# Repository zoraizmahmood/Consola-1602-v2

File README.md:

# Consola 1602 · v2

> La segunda versión de la [Consola 1602](https://github.com/zoraizmahmood/Consola-1602): el mismo firmware, pero ahora sobre una **PCB propia** diseñada en KiCad y fabricada por **PCBWay**. Adiós a la protoboard y a los cables sueltos.

<p align="center"><sub>El LCD y los botones colocados en su sitio, todavía sin soldar (ver <a href="#estado-del-montaje">estado del montaje</a>).</sub></p>

La v1 era un Arduino Uno, un LCD de 16x2, cinco botones y un zumbador unidos con cables dupont. Funcionaba, pero cualquier golpe soltaba un cable y no había forma de meterla en una caja decente. La v2 convierte todo ese cableado en un **shield** que se enchufa directamente encima del Arduino Uno: un único bloque compacto que entra en una carcasa a medida.

---

## Qué cambia respecto a la v1

| | v1 | v2 |
|---|---|---|
| Montaje | Protoboard y cables dupont | Shield PCB de dos capas que se enchufa al Uno |
| Contraste del LCD | Potenciómetro de 10 kΩ | Sin potenciómetro: V0 conectado a D8 |
| Zumbador | D8 | A2 |
| Resistencia de la retro | 220 Ω de inserción | R1 SMD 0805 (ver [lo que cambiaría](#mi-experiencia-con-pcbway)) |
| Carcasa | Pensada para el Uno suelto | Nueva, a medida de la PCB |
| Firmware | v1.1 | v2.0 (mismas aplicaciones, pines adaptados) |

Todas las aplicaciones de la v1 siguen ahí: reloj con dígitos grandes, Snake, Dino, Simon, test de reflejos, Pomodoro, notas, diagnóstico del sistema y ajustes en EEPROM. La documentación completa del firmware y su arquitectura está en el [repositorio de la v1](https://github.com/zoraizmahmood/Consola-1602#arquitectura).

---

## La placa

<p align="center"><sub>La placa tal como llegó de PCBWay: máscara negra y serigrafía blanca. Cara superior a la izquierda, inferior a la derecha.</sub></p>

<p align="center"><sub>El mismo diseño renderizado en KiCad antes de mandarlo a fabricar.</sub></p>

| Característica      | Valor                          |
|---------------------|--------------------------------|
| Tamaño              | 85,9 × 61,9 mm                 |
| Capas               | 2                              |
| Grosor              | 1,6 mm                         |
| Pista mínima        | 0,25 mm                        |
| Separación mínima   | 0,2 mm                         |
| Vías                | 9                              |
| Herramienta         | KiCad 10                       |
| Fabricante          | [PCBWay](https://www.pcbway.com) |

Los cinco botones forman una cruceta a la izquierda (`◄` `▲` `▼` `►`) y el `OK` queda solo a la derecha, como en un mando. El LCD ocupa toda la mitad superior y los conectores del Arduino quedan debajo, de modo que la placa se monta directamente encima del Uno.

### Archivos

| Ruta | Qué es |
|------|--------|
| [`hardware/pcb/placa.kicad_pro`](hardware/pcb/placa.kicad_pro) | Proyecto de KiCad |
| [`hardware/pcb/placa.kicad_sch`](hardware/pcb/placa.kicad_sch) | Esquema |
| [`hardware/pcb/placa.kicad_pcb`](hardware/pcb/placa.kicad_pcb) | Diseño de la placa |
| [`hardware/pcb/gerbers/`](hardware/pcb/gerbers/) | Gerber y taladros sueltos |
| [`hardware/pcb/gerbers-pcbway.zip`](hardware/pcb/gerbers-pcbway.zip) | El ZIP exacto que se subió a PCBWay |
| [`assets/esquema.pdf`](assets/esquema.pdf) | Esquema en PDF, para verlo sin KiCad |

### Pedir tu propia placa

1. Descarga [`gerbers-pcbway.zip`](hardware/pcb/gerbers-pcbway.zip).
2. Súbelo en el presupuesto rápido de PCBWay (o de cualquier otro fabricante: son Gerber estándar).
3. Las opciones por defecto valen: 2 capas, 1,6 mm, FR-4. El color de la máscara es a tu gusto.

---

## Mi experiencia con PCBWay

Esta versión existe gracias a que **PCBWay patrocinó la fabricación de las placas**. Lo dejo claro desde el principio: no he pagado las PCB. Lo que cuento aquí es mi experiencia real, incluido lo que cambiaría (que es culpa mía, no de ellos).

### Cronología

| Fecha        | Qué pasó                                                              |
|--------------|-----------------------------------------------------------------------|
| 13 de agosto | PCBWay se pone en contacto conmigo tras ver la v1                     |
| 17 de agosto | Diseño terminado en KiCad y Gerber listos                             |
| 18 de agosto | Pedido registrado                                                     |
| 19 de agosto | Placas fabricadas y enviadas                                          |

**Del primer correo a tener los Gerber pasaron solo cuatro días**, y desde que se registró el pedido hasta que salió de fábrica, **poco más de un día**.

**Diseñar la primera PCB.** Hasta ahora todo lo había montado en protoboard, así que pasar a KiCad fue empezar de cero: esquema, asignar huellas, colocar componentes y rutar pistas. Lo más difícil no fue el rutado, sino decidir dónde iba cada cosa para que la placa encajara sobre el Arduino Uno y a la vez quedara cómoda en la mano.

**El pedido.** Subí el ZIP con los Gerber y del resto se encargó su equipo de atención al cliente. Pedí cinco placas en FR-4 de dos capas, 1,6 mm, acabado HASL y **máscara negra con serigrafía blanca**. PCBWay se hizo cargo también del IVA, así que el paquete llegó a Barcelona sin sorpresas en la aduana.

**La calidad: excelente.** El paquete llegó **perfectamente empaquetado** y las placas, impecables: la serigrafía se lee nítida hasta en los textos más pequeños, la máscara negra está bien alineada con los pads y todos los taladros encajan con los componentes. El acabado negro queda muy bien; parece un producto de verdad, no un prototipo.

**Lo que cambiaría.** La resistencia de la retroiluminación (R1). En el diseño elegí una huella **SMD 0805**, una de esas resistencias diminutas que se sueldan con estación de aire caliente o con mucho pulso, en vez de una resistencia normal de patillas. Es la única pieza SMD de la placa: todo lo demás es de inserción. En la próxima versión usaré una resistencia de inserción (huella `R_Axial_DIN0207`), para que toda la placa se pueda montar con un soldador básico. Si te fijas en los Gerber (`placa-F_Cu.gbr`) o en la foto de la cara superior, son los dos pads pequeños marcados como `R1` junto al zumbador.

### Estado del montaje

**La placa todavía no está soldada.** Tengo todos los componentes, pero mi soldador es bastante malo y no está a la altura de esta placa. Intentándolo **estropeé dos de las cinco placas**. Eso es culpa de mi herramienta y de mi técnica, no de las placas: las otras tres siguen perfectas.

Cuando tenga un soldador mejor (de temperatura regulable y punta fina), montaré una de las tres que quedan y actualizaré este README con fotos de la consola terminada y funcionando. Mientras tanto, el firmware se puede probar en el simulador con el [`diagram.json`](diagram.json).

**En resumen:** pasar de la protoboard a una PCB fabricada ha sido el salto más grande del proyecto. Ver tu propio diseño convertido en una placa real, con tu nombre en la serigrafía, es otra cosa. Si estás pensando en hacer tu primera PCB, hazla.

<p align="center"><sub>El lote recién sacado del paquete.</sub></p>

---

## Materiales

| Componente                              | Ref.      | Cantidad |
|-----------------------------------------|-----------|----------|
| PCB Consola 1602 v2                     | —         | 1        |
| Arduino Uno R3                          | —         | 1        |
| LCD 16x2 con HD44780 (WC1602A o similar)| LCD1      | 1        |
| Pulsador táctil 6×6 mm de inserción     | SW1–SW5   | 5        |
| Zumbador activo de 5 V, 12 mm           | BZ1       | 1        |
| Resistencia 220 Ω, SMD 0805 ⚠️          | R1        | 1        |
| Tira de pines de 2,54 mm 1x8            | J1, J4    | 2        |
| Tira de pines de 2,54 mm 1x10           | J2        | 1        |
| Tira de pines de 2,54 mm 1x6            | J3        | 1        |

Ya no hace falta el potenciómetro de 10 kΩ ni la protoboard.

> ⚠️ **R1 es SMD (0805)**, la única pieza de montaje superficial. Para soldarla viene bien una estación de aire caliente, o un soldador de punta fina con pinzas y flux.

---

## Conexiones

En la v2 el cableado lo fija la placa, pero conviene tenerlo a mano para depurar:

| Señal                | Pin del Uno | En la PCB |
|----------------------|-------------|-----------|
| LCD `RS`             | D12         | LCD1-4    |
| LCD `E`              | D11         | LCD1-6    |
| LCD `D4–D7`          | D5, D4, D3, D2 | LCD1-11…14 |
| LCD `V0` (contraste) | D8          | LCD1-3    |
| LCD `A` (retro)      | D9 a través de R1 | LCD1-15 |
| `▲`                  | D6          | SW2       |
| `▼`                  | D7          | SW4       |
| `◄`                  | D10         | SW1       |
| `►`                  | A0          | SW3       |
| `OK`                 | A1          | SW5       |
| Zumbador             | A2          | BZ1       |

**Sobre el contraste:** la v1 usaba un potenciómetro en `V0`. En la placa ese pin va a D8 y el firmware lo pone a `LOW`, que equivale a contraste máximo y en los LCD de 5 V se lee bien. Así la placa se queda sin una pieza y sin un ajuste que hacer a mano.

Los pines **A4** y **A5** siguen libres para añadir un RTC DS3231.

---

## Carcasa

La carcasa de la v2 está rediseñada a medida de la PCB: una bandeja de 91,75 × 67,75 × 20,6 mm con esquinas redondeadas, un reborde interior en el borde superior, dos tetones de fijación en el fondo y una ventana lateral para los conectores.

| Archivo | Formato | Para qué sirve |
|---------|---------|----------------|
| [`hardware/carcasa/carcasa-v2.step`](hardware/carcasa/carcasa-v2.step) | STEP | Sólido editable en cualquier CAD (Fusion 360, FreeCAD, Onshape…) |
| [`hardware/carcasa/carcasa-v2.3mf`](hardware/carcasa/carcasa-v2.3mf) | 3MF | Listo para abrir en el laminador (Bambu Studio, PrusaSlicer, Cura…) |

### Ajustes de impresión

| Parámetro          | Valor        |
|--------------------|--------------|
| Material           | PLA          |
| Altura de capa     | 0,2 mm       |
| Relleno            | 20 %         |
| Soportes           | No           |
| Perímetros         | 3            |

---

## Cargar el firmware

Solo hace falta la librería `LiquidCrystal`, que viene incluida en el IDE de Arduino.

```bash
git clone https://github.com/zoraizmahmood/Consola-1602-v2.git
cd Consola-1602-v2

arduino-cli compile --fqbn arduino:avr:uno .
arduino-cli upload  --fqbn arduino:avr:uno -p /dev/ttyACM0 .
```

También puedes abrir `Consola-1602-v2.ino` en el IDE de Arduino y subirlo con `Ctrl+U`.

| Recurso                  | Uso      | Máximo del Uno | Ocupación |
|--------------------------|----------|----------------|-----------|
| Memoria de programa      | 15 238 B | 32 256 B       | 47 %      |
| RAM (variables globales) | 622 B    | 2 048 B        | 30 %      |

El [`diagram.json`](diagram.json) de [Wokwi](https://wokwi.com) está actualizado al cableado de la v2, así que puedes probar el firmware en el navegador antes de soldar nada.

---

## Estructura del proyecto

```
Consola-1602-v2/
├── Consola-1602-v2.ino      # Firmware adaptado a la PCB
├── diagram.json             # Cableado para el simulador de Wokwi
├── wokwi.toml
├── hardware/
│   ├── pcb/
│   │   ├── placa.kicad_pro  # Proyecto de KiCad
│   │   ├── placa.kicad_sch  # Esquema
│   │   ├── placa.kicad_pcb  # Diseño de la placa
│   │   ├── gerbers/         # Gerber y taladros
│   │   └── gerbers-pcbway.zip
│   └── carcasa/
│       ├── carcasa-v2.step  # Sólido editable
│       └── carcasa-v2.3mf   # Listo para laminar
├── assets/                  # Fotos, renders y esquema en PDF
└── .github/workflows/
    └── build.yml            # Compilación automática para arduino:avr:uno
```

---

## Agradecimientos

A [PCBWay](https://www.pcbway.com) por patrocinar la fabricación de las placas de esta versión.

## Autor

Creado por [zoraizmahmood](https://github.com/zoraizmahmood).

## Licencia

El firmware, bajo licencia [MIT](LICENSE). El hardware de `hardware/` (PCB y carcasa), bajo [CC BY 4.0](https://creativecommons.org/licenses/by/4.0/deed.es).

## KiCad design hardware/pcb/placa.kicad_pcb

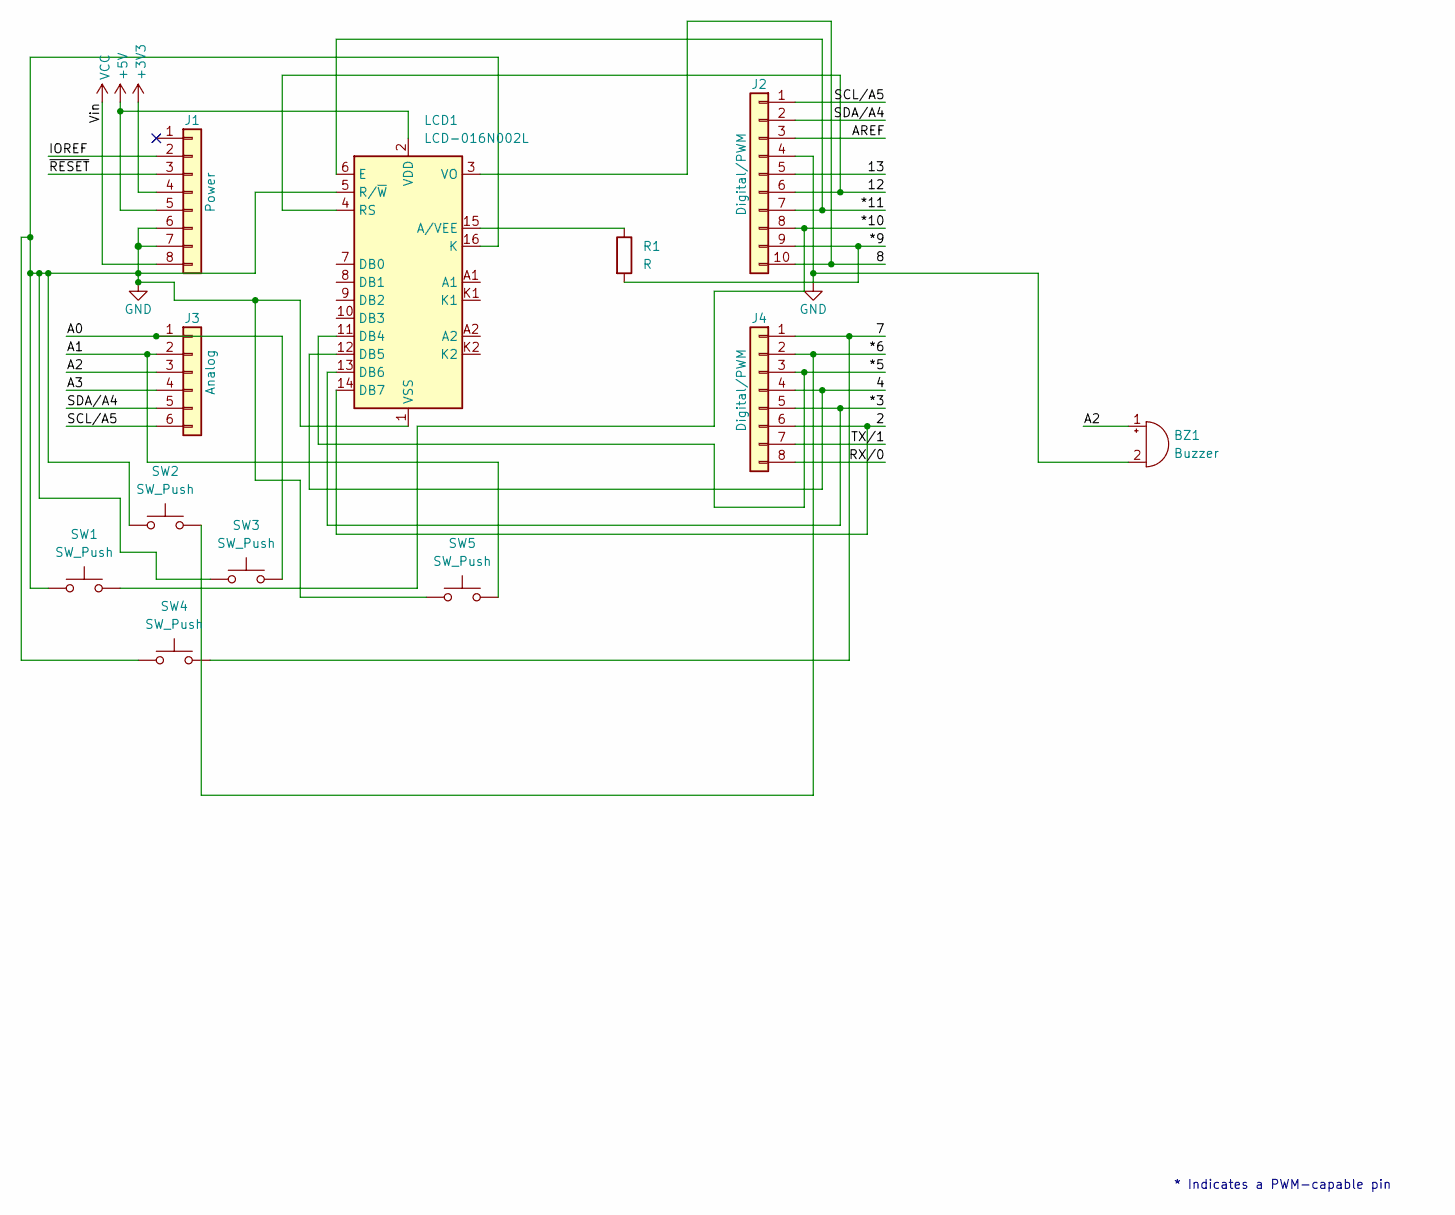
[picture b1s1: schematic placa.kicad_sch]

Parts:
BZ1: Buzzer; Buzzer_12x9.5RM7.6
J1: Power; PinSocket_1x08_P2.54mm_Vertical
J2: Digital/PWM; PinSocket_1x10_P2.54mm_Vertical
J3: Analog; PinSocket_1x06_P2.54mm_Vertical
J4: Digital/PWM; PinSocket_1x08_P2.54mm_Vertical
LCD1: LCD-016N002L; WC1602A
R1: R; R_0805_2012Metric_Pad1.20x1.40mm_HandSolder
SW1, SW2, SW3, SW4, SW5: SW_Push; SW_PUSH_6mm

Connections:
+3V3: J1.4
+5V: J1.5, LCD1.2 (VDD)
/2: J4.6, LCD1.14 (DB7)
/4: J4.4, LCD1.12 (DB5)
/7: J4.1, SW4.2
/8: J2.10, LCD1.3 (VO)
/12: J2.6, LCD1.4 (RS)
/13: J2.5
/*3: J4.5, LCD1.13 (DB6)
/*5: J4.3, LCD1.11 (DB4)
/*6: J4.2, SW2.2
/*10: J2.8, SW1.2
/*11: J2.7, LCD1.6 (E)
/A0: J3.1, SW3.2
/A1: J3.2, SW5.2
/A2: BZ1.1 (+), J3.3
/A3: J3.4
/AREF: J2.3
/IOREF: J1.2
/RX/0: J4.8
/SCL/A5: J2.1, J3.6
/SDA/A4: J2.2, J3.5
/TX/1: J4.7
/~RESET: J1.3
unnamed: LCD1.15 (A/VEE), R1.1
VCC: J1.8

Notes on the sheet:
* Indicates a PWM-capable pin

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
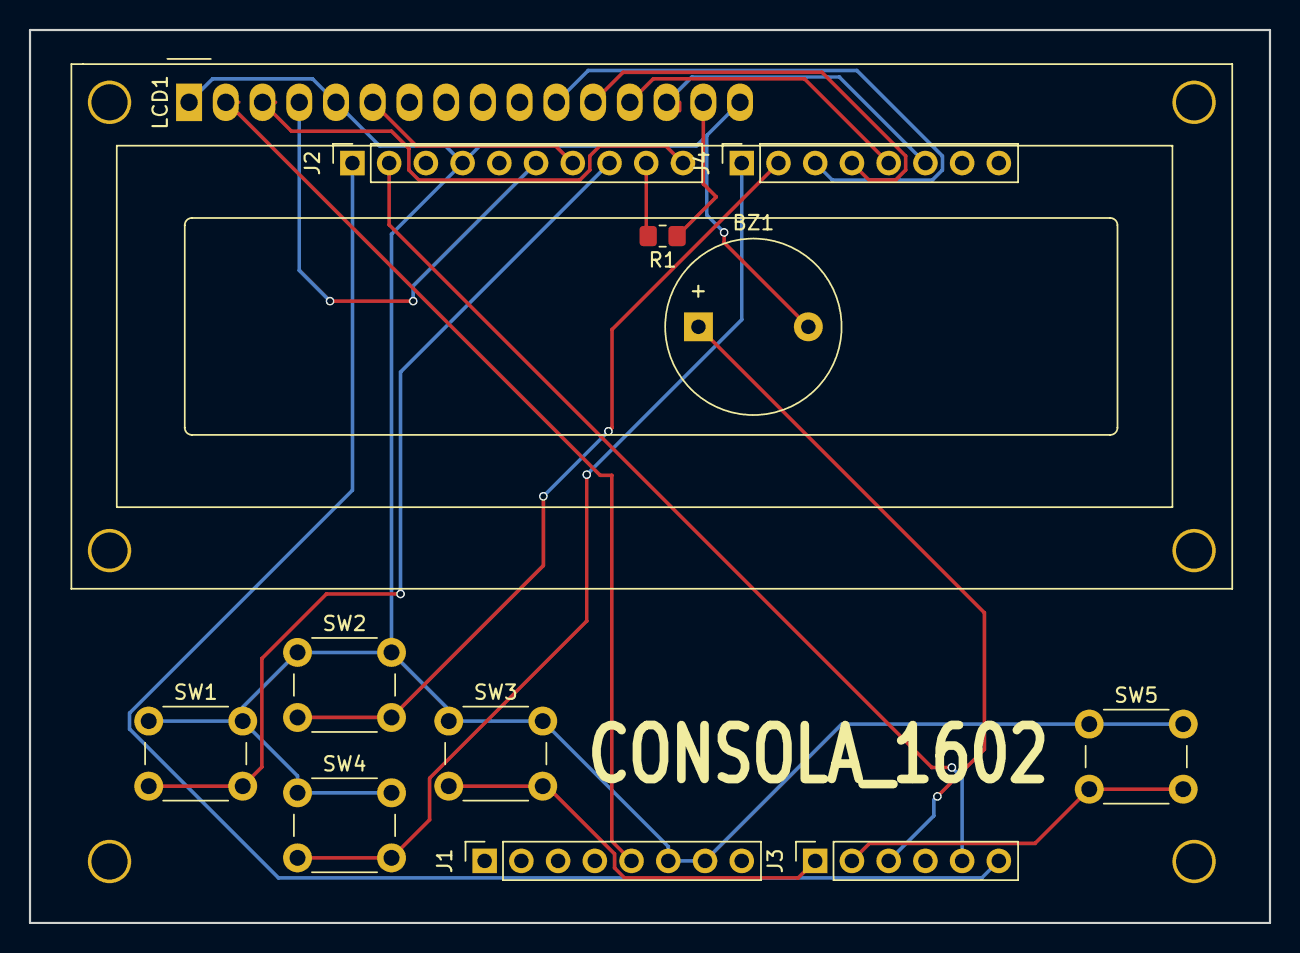
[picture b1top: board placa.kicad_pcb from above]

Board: 2 copper layers, 85.8 x 61.8 mm, 12 parts (0 on the bottom side), 19 nets.
